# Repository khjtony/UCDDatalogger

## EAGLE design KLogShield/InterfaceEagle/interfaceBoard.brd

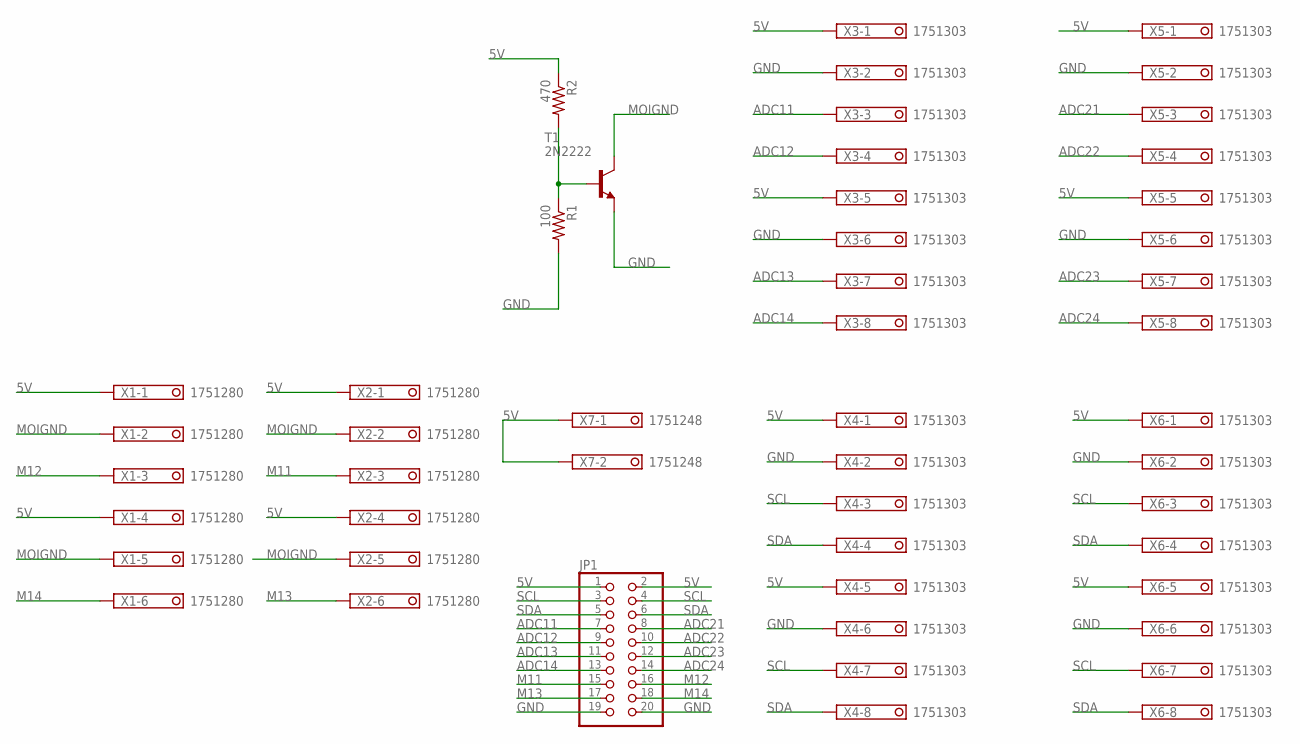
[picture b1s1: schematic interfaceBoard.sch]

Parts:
JP1: PINHD-2X10; 2X10
R1: 100; M0805
R2: 470; M0805
T1: 2N2222; TO92-EBC-OVAL
X1, X2: 1751280
X3, X4, X5, X6: 1751303
X7: 1751248

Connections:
5V: JP1.1, JP1.2, R2.1, X1.1, X1.4, X2.1, X2.4, X3.1, X3.5, X4.1, X4.5, X5.1, X5.5, X6.1, X6.5, X7.1, X7.2
ADC11: JP1.7, X3.3
ADC12: JP1.9, X3.4
ADC13: JP1.11, X3.7
ADC14: JP1.13, X3.8
ADC21: JP1.8, X5.3
ADC22: JP1.10, X5.4
ADC23: JP1.12, X5.7
ADC24: JP1.14, X5.8
GND: JP1.19, JP1.20, R1.2, T1.E, X3.2, X3.6, X4.2, X4.6, X5.2, X5.6, X6.2, X6.6
M11: JP1.15, X2.3
M12: JP1.16, X1.3
M13: JP1.17, X2.6
M14: JP1.18, X1.6
MOIGND: T1.C, X1.2, X1.5, X2.2, X2.5
unnamed: R1.1, R2.2, T1.B
SCL: JP1.3, JP1.4, X4.3, X4.7, X6.3, X6.7
SDA: JP1.5, JP1.6, X4.4, X4.8, X6.4, X6.8

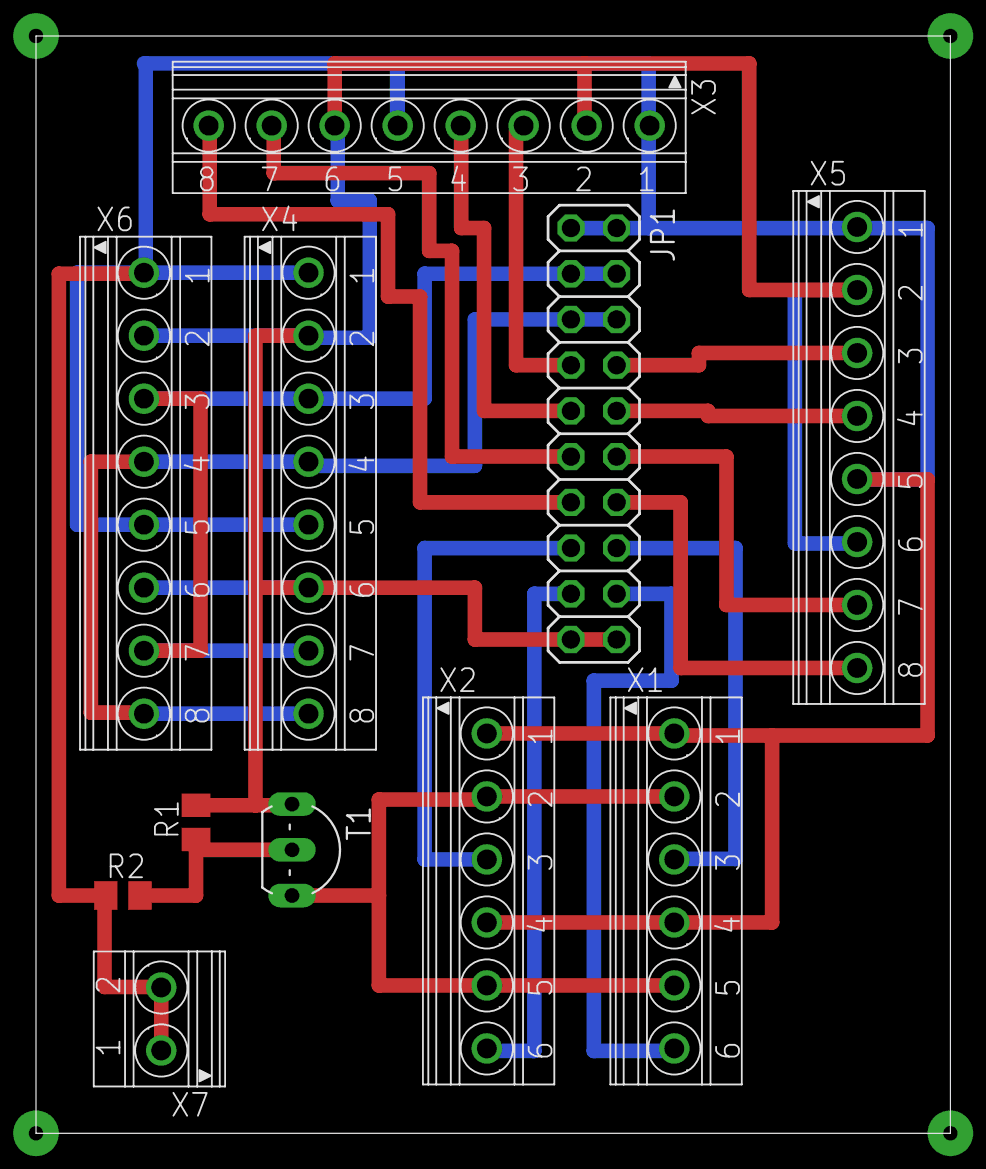
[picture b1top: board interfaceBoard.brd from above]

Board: 2 copper layers, 50.8 x 61.0 mm, 11 parts (0 on the bottom side), 18 nets.

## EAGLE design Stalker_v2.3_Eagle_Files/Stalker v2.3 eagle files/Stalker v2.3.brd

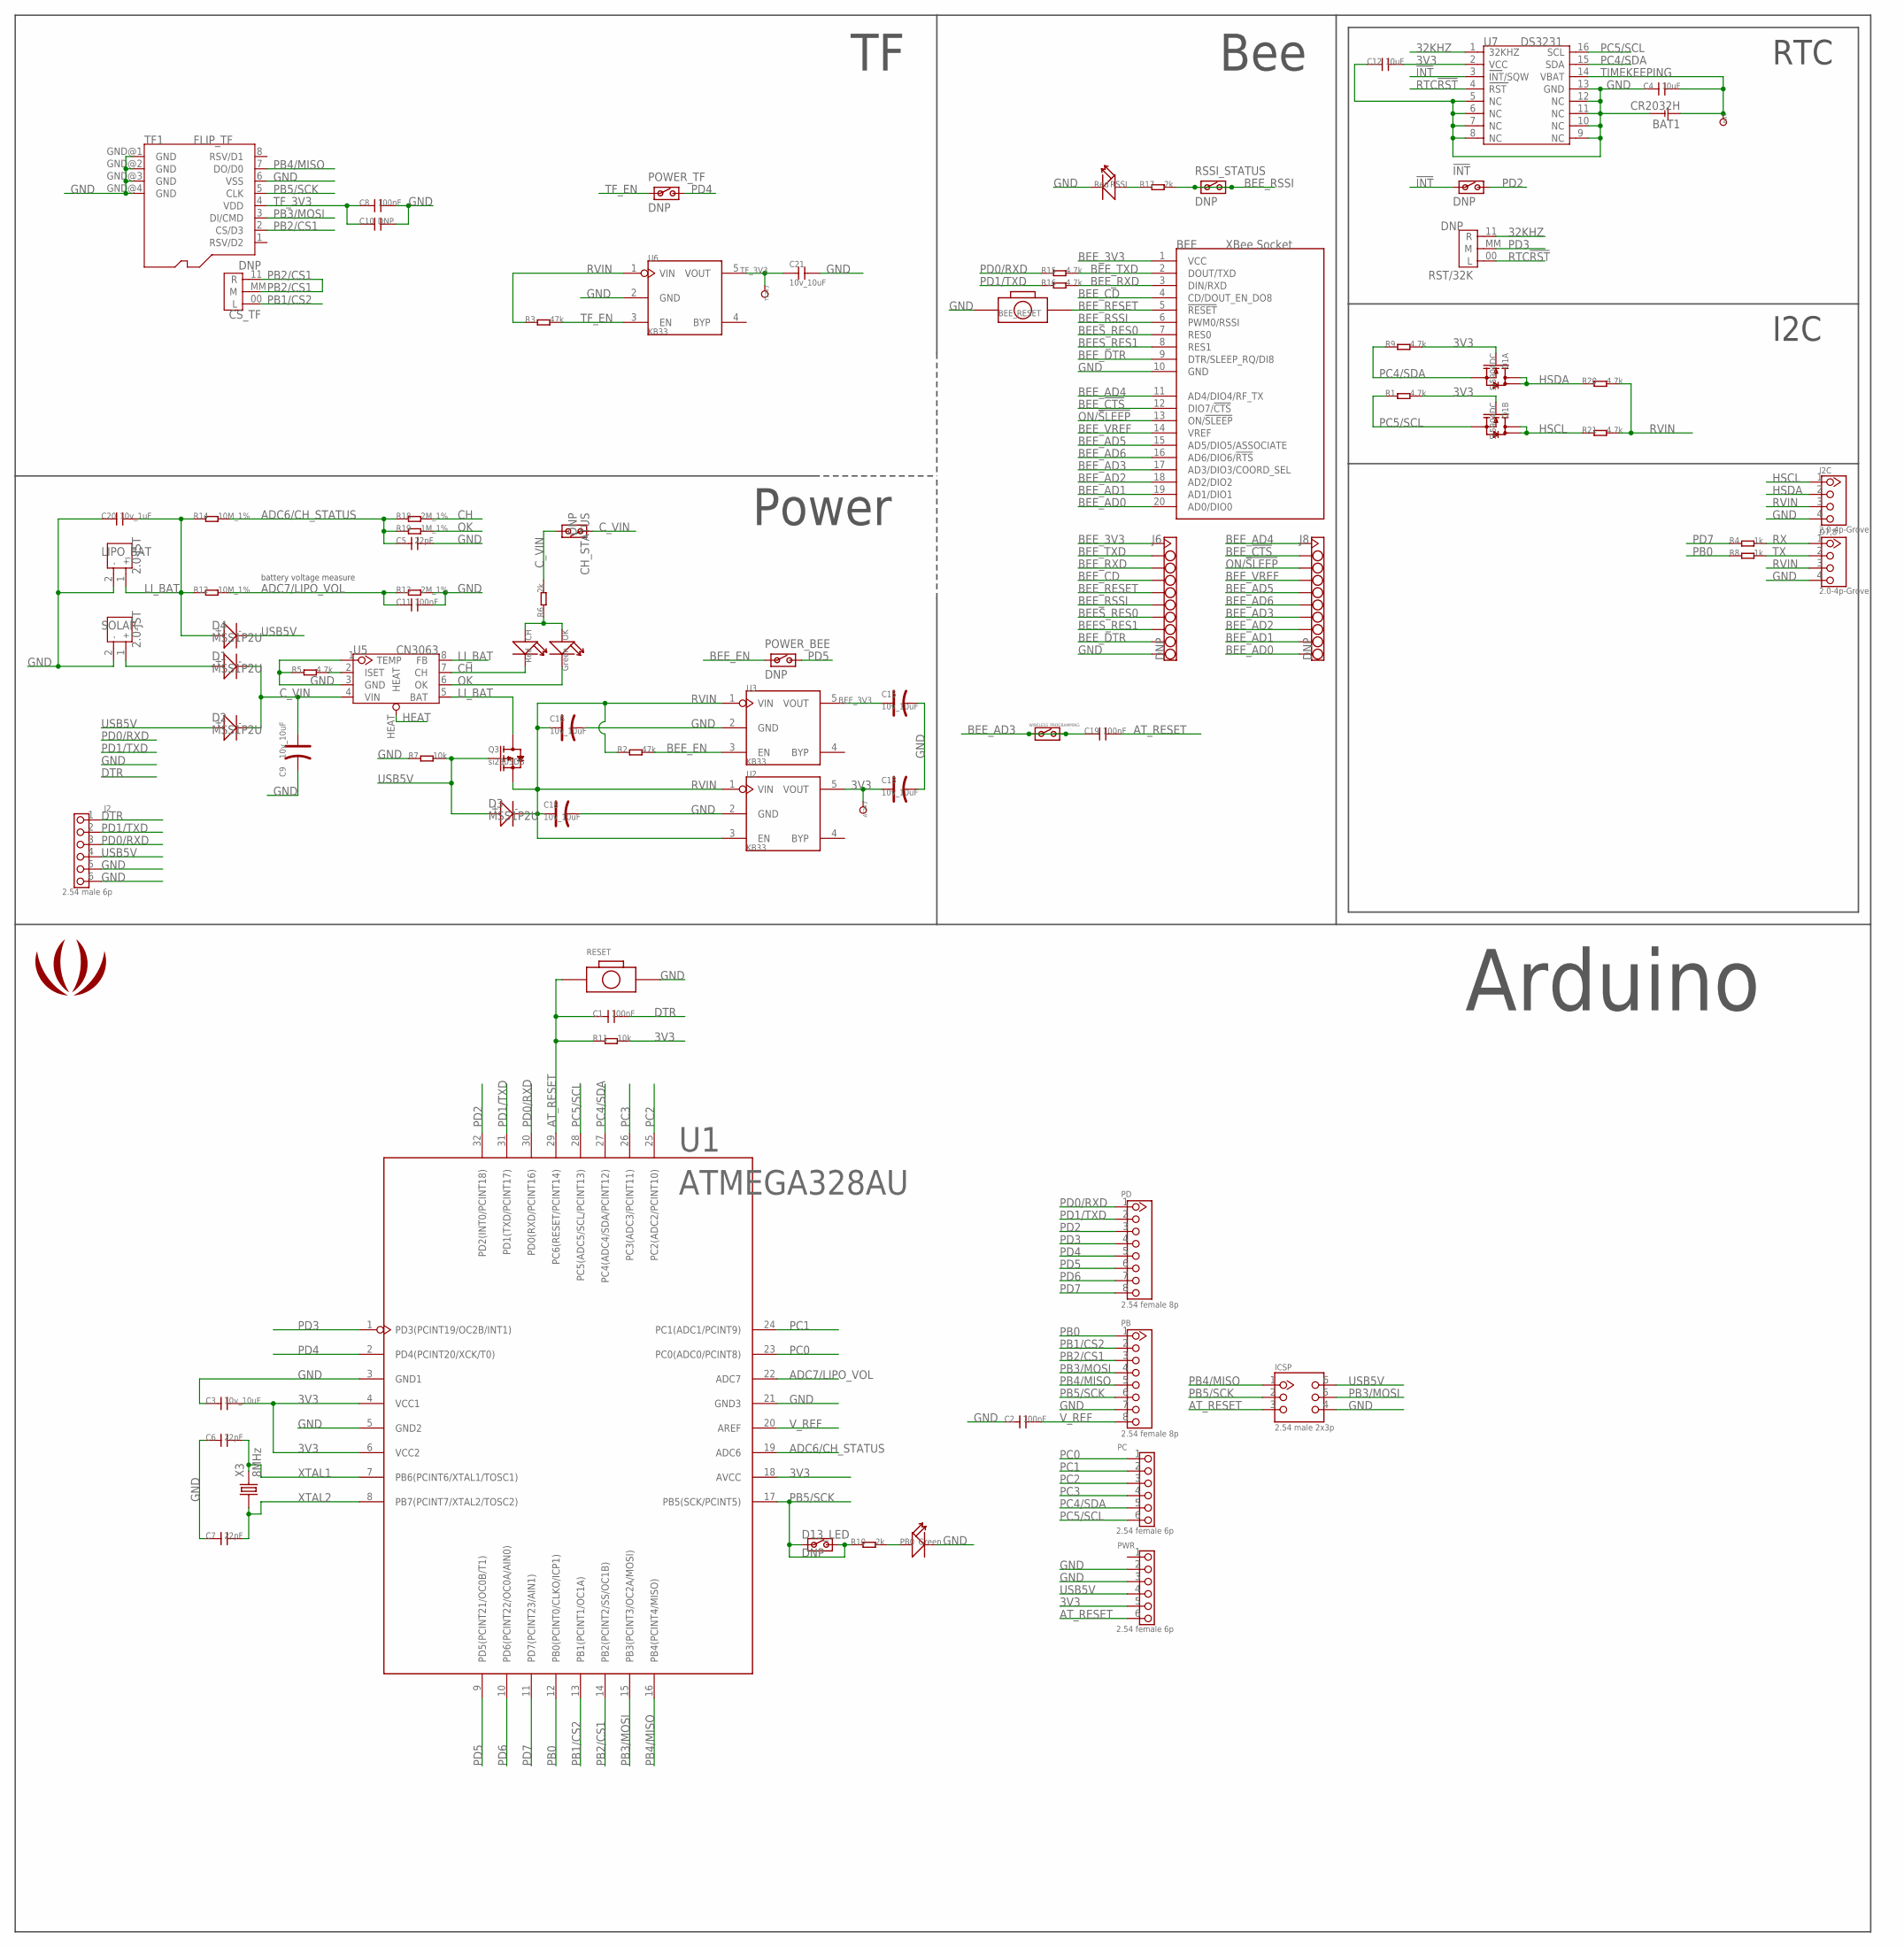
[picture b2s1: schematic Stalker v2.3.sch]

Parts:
!INT: DNP; JP_SW
AT3V3: DNP; TP_3535
BAT: DNP; TP_3535
BAT1: CR2032H
BEE: XBee Socket; BEE
BEE_RESET: 3.8x6.1 button; BOTTON_1
C1, C2, C8, C11, C19: 100nF; 0603
C3, C21: 10v_10uF; 0805
C4, C12: 10uF; 0805
C5, C6, C7: 22pF; 0603
C9, C13, C15, C16, C18: 10v_10uF; AVX-A
C10: DNP; 0603
C20: 10v_1uF; 0805
CH: Red; D0603
CH_STATUS: DNP; JP_SW
CS_TF: DNP; JUMPER
D1, D2, D3, D4: MSS1P2U; D1005
D7,8: 2.0-4p-Grove; 4P-2.0
D13_LED: DNP; JP_SW
I2C: 2.0-4p-Grove; 4P-2.0
ICSP: 2.54 male 2x3p; 2X3P-2.54-LEADED
J2: 2.54 male 6p; 6P-2.54-LEADED
J6, J8: DNP; HEADER_1X10
LIPO_BAT: 2.0-JST; JST-2.0
LOGO1: LOGO; LOGO_RO
OK: Green; D0603
PB: 2.54 female 8p; 8P-2.54-LEADED
PB0: Green; D0603
PC: 2.54 female 6p; 6P-2.54-LEADED
PD: 2.54 female 8p; 8P-2.54-LEADED
POWER_BEE: DNP; JP_SW
POWER_TF: DNP; JP_SW
PWR: 2.54 female 6p; 6P-2.54-LEADED
Q1: Si5904DC; 1206-8
Q3: si2305DS; SOT23
R1, R5, R9, R15, R16, R20, R21: 4.7k; 0603@1
R2, R3: 47k; 0603@1
R4, R8: 1k; 0603@1
R6, R10, R17: 2k; 0603@1
R7, R11: 10k; 0603@1
R12, R14: 10M_1%; 0603@1
R13, R18: 2M_1%; 0603@1
R19: 1M_1%; 0603@1
RESET: 3.8x6.1 button; BOTTON_1
RSSI: Red; D0603
RSSI_STATUS: DNP; JP_SW
RST/32K: DNP; JUMPER
SOLAR: 2.0-JST; JST-2.0
TF1: FLIP_TF
TF3V3: DNP; TP_3535
U1: ATMEGA328AU; ATMEGA168-20AU
U2, U3, U6: KB33; SOT23-5
U5: CN3063; SOP8
U7: DS3231; SO16-W
WIRELESS_PROGRAMMING: DNP; JP_SW
X3: 8MHz; HC49/S

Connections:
3V3: AT3V3.T, C3.2, C12.2, C13.+, PWR.5, Q1.2 (G), Q1.4 (G), R1.2, R9.2, R11.2, U1.4 (VCC1), U1.6 (VCC2), U1.18 (AVCC), U2.5 (VOUT), U7.2 (VCC)
32KHZ: RST/32K.11 (R), U7.1 (32KHZ)
!INT: !INT.1, U7.3 (INT/SQW)
ADC6/CH_STATUS: C5.1, R14.2, R18.1, R19.1, U1.19 (ADC6)
ADC7/LIPO_VOL: C11.1, R12.2, R13.1, U1.22 (ADC7)
AT_RESET: C1.1, C19.2, ICSP.3, PWR.6, R11.1, RESET.1, U1.29 (PC6(RESET/PCINT14))
BEES_RES0: BEE.7 (RES0), J6.7
BEES_RES1: BEE.8 (RES1), J6.8
BEE_3V3: BEE.1 (VCC), C15.+, J6.1, U3.5 (VOUT)
BEE_!CTS: BEE.12 (DIO7/!CTS), J8.2
BEE_AD0: BEE.20 (AD0/DIO0), J8.10
BEE_AD1: BEE.19 (AD1/DIO1), J8.9
BEE_AD2: BEE.18 (AD2/DIO2), J8.8
BEE_AD3: BEE.17 (AD3/DIO3/COORD_SEL), C19.1, J8.7, WIRELESS_PROGRAMMING.1, WIRELESS_PROGRAMMING.2
BEE_AD4: BEE.11 (AD4/DIO4/RF_TX), J8.1
BEE_AD5: BEE.15 (AD5/DIO5/ASSOCIATE), J8.5
BEE_AD6: BEE.16 (AD6/DIO6/!RTS), J8.6
BEE_CD: BEE.4 (CD/DOUT_EN_DO8), J6.4
BEE_DTR: BEE.9 (DTR/SLEEP_RQ/DI8), J6.9
BEE_EN: POWER_BEE.1, R2.2, U3.3 (EN)
BEE_RESET: BEE.5 (!RESET), BEE_RESET.P$2 (2), J6.5
BEE_RSSI: BEE.6 (PWM0/RSSI), J6.6, R17.2, RSSI_STATUS.1, RSSI_STATUS.2
BEE_RXD: BEE.3 (DIN/RXD), J6.3, R16.2
BEE_TXD: BEE.2 (DOUT/TXD), J6.2, R15.2
BEE_VREF: BEE.14 (VREF), J8.4
CH: CH.-, R18.2, U5.7 (CH)
C_VIN: C9.+, CH_STATUS.1, CH_STATUS.2, D1.-, D2.-, R6.2, U5.4 (VIN)
DTR: C1.2, J2.1
GND: BAT1.-, BEE.10 (GND), BEE_RESET.1, C2.1, C3.1, C4.1, C5.2, C6.1, C7.1, C8.2, C9.-, C10.2, C11.2, C12.1, C13.-, C15.-, C16.-, C18.-, C20.1, C21.2, D7,8.4, I2C.4, ICSP.4, J2.5, J2.6, J6.10, LIPO_BAT.2, PB.7, PB0.-, PWR.2, PWR.3, R5.1, R7.1, R13.2, RESET.P$2 (2), RSSI.-, SOLAR.2, TF1.6 (VSS), TF1.GND@1 (GND), TF1.GND@2 (GND), TF1.GND@3 (GND), TF1.GND@4 (GND), U1.3 (GND1), U1.5 (GND2), U1.21 (GND3), U2.2 (GND), U3.2 (GND), U5.1 (TEMP), U5.3 (GND), U6.2 (GND), U7.5 (NC), U7.6 (NC), U7.7 (NC), U7.8 (NC), U7.9 (NC), U7.10 (NC), U7.11 (NC), U7.12 (NC), U7.13 (GND)
HEAT: U5.HEAT
HSCL: I2C.1, Q1.5 (D), Q1.6 (D), R21.1
HSDA: I2C.2, Q1.7 (D), Q1.8 (D), R20.1
LI_BAT: C20.2, D4.+, LIPO_BAT.1, Q3.3 (D), R12.1, R14.1, U5.5 (BAT), U5.8 (FB)
unnamed: PB0.+, R10.2
unnamed: D1.+, SOLAR.1
unnamed: R5.2, U5.2 (ISET)
unnamed: R17.1, RSSI.+
unnamed: CH.+, OK.+, R6.1
OK: OK.-, R19.2, U5.6 (OK)
ON/!SLEEP: BEE.13 (ON/!SLEEP), J8.3
PB0: PB.1, R8.1, U1.12 (PB0(PCINT0/CLKO/ICP1))
PB1/CS2: CS_TF.00 (L), PB.2, U1.13 (PB1(PCINT1/OC1A))
PB2/CS1: CS_TF.11 (R), CS_TF.MM (M), PB.3, TF1.2 (CS/D3), U1.14 (PB2(PCINT2/SS/OC1B))
PB3/MOSI: ICSP.5, PB.4, TF1.3 (DI/CMD), U1.15 (PB3(PCINT3/OC2A/MOSI))
PB4/MISO: ICSP.1, PB.5, TF1.7 (DO/D0), U1.16 (PB4(PCINT4/MISO))
PB5/SCK: D13_LED.1, D13_LED.2, ICSP.2, PB.6, R10.1, TF1.5 (CLK), U1.17 (PB5(SCK/PCINT5))
PC0: PC.1, U1.23 (PC0(ADC0/PCINT8))
PC1: PC.2, U1.24 (PC1(ADC1/PCINT9))
PC2: PC.3, U1.25 (PC2(ADC2/PCINT10))
PC3: PC.4, U1.26 (PC3(ADC3/PCINT11))
PC4/SDA: PC.5, Q1.1 (S), R9.1, U1.27 (PC4(ADC4/SDA/PCINT12)), U7.15 (SDA)
PC5/SCL: PC.6, Q1.3 (S), R1.1, U1.28 (PC5(ADC5/SCL/PCINT13)), U7.16 (SCL)
PD0/RXD: J2.3, PD.1, R15.1, U1.30 (PD0(RXD/PCINT16))
PD1/TXD: J2.2, PD.2, R16.1, U1.31 (PD1(TXD/PCINT17))
PD2: !INT.2, PD.3, U1.32 (PD2(INT0/PCINT18))
PD3: PD.4, RST/32K.MM (M), U1.1 (PD3(PCINT19/OC2B/INT1))
PD4: PD.5, POWER_TF.2, U1.2 (PD4(PCINT20/XCK/T0))
PD5: PD.6, POWER_BEE.2, U1.9 (PD5(PCINT21/OC0B/T1))
PD6: PD.7, U1.10 (PD6(PCINT22/OC0A/AIN0))
PD7: PD.8, R4.1, U1.11 (PD7(PCINT23/AIN1))
RTC!RST: RST/32K.00 (L), U7.4 (RST)
RVIN: C16.+, C18.+, D3.-, D7,8.3, I2C.3, Q3.2 (S), R2.1, R3.1, R20.2, R21.2, U2.1 (VIN), U2.3 (EN), U3.1 (VIN), U6.1 (VIN)
RX: D7,8.1, R4.2
TF_3V3: C8.1, C10.1, C21.1, TF1.4 (VDD), TF3V3.T, U6.5 (VOUT)
TF_EN: POWER_TF.1, R3.2, U6.3 (EN)
TIMEKEEPING: BAT.T, BAT1.+, C4.2, U7.14 (VBAT)
TX: D7,8.2, R8.2
USB5V: D2.+, D3.+, D4.-, ICSP.6, J2.4, PWR.4, Q3.1 (G), R7.2
V_REF: C2.2, PB.8, U1.20 (AREF)
XTAL1: C6.2, U1.7 (PB6(PCINT6/XTAL1/TOSC1)), X3.2
XTAL2: C7.2, U1.8 (PB7(PCINT7/XTAL2/TOSC2)), X3.1

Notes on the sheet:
Power
Arduino
Bee
battery voltage measure
RTC
I2C

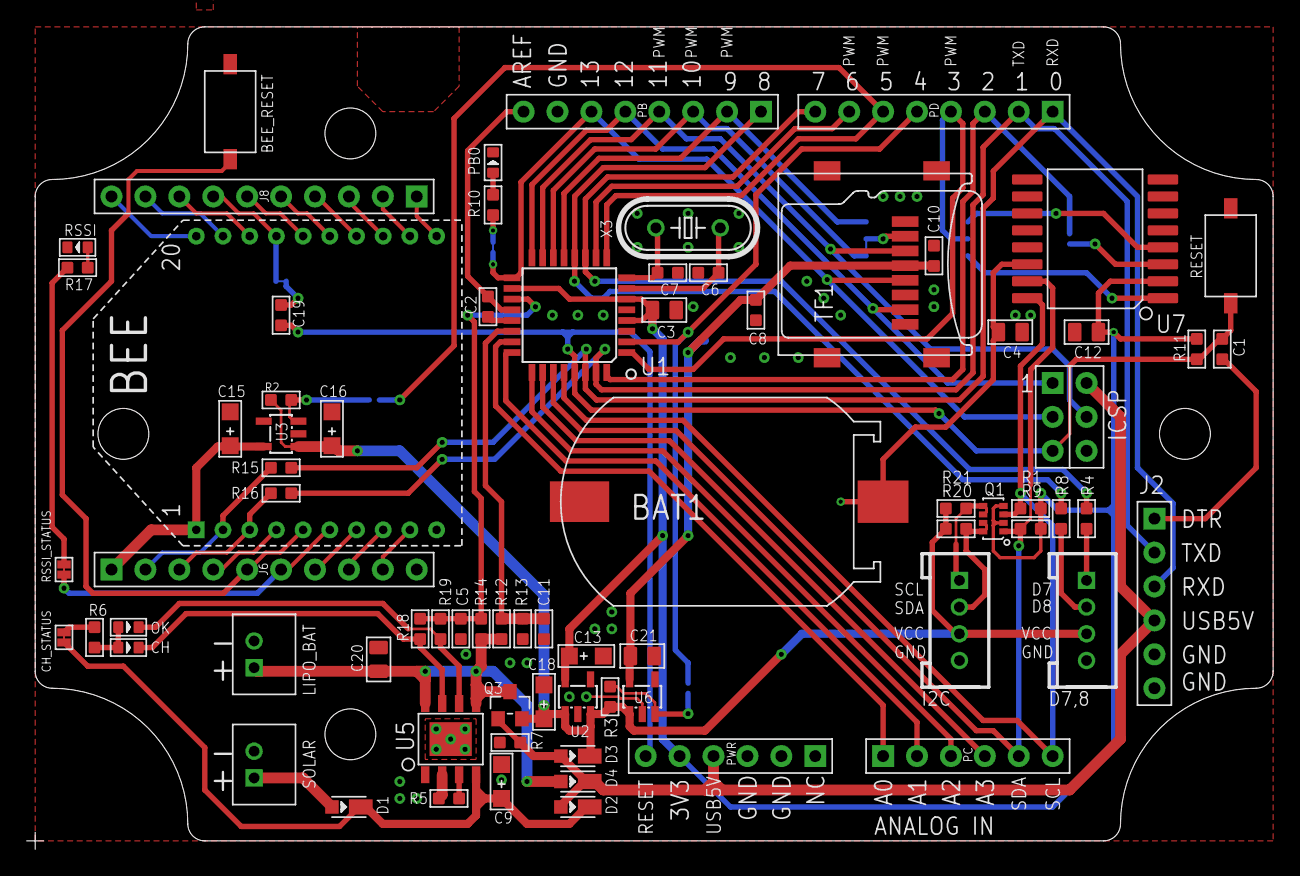
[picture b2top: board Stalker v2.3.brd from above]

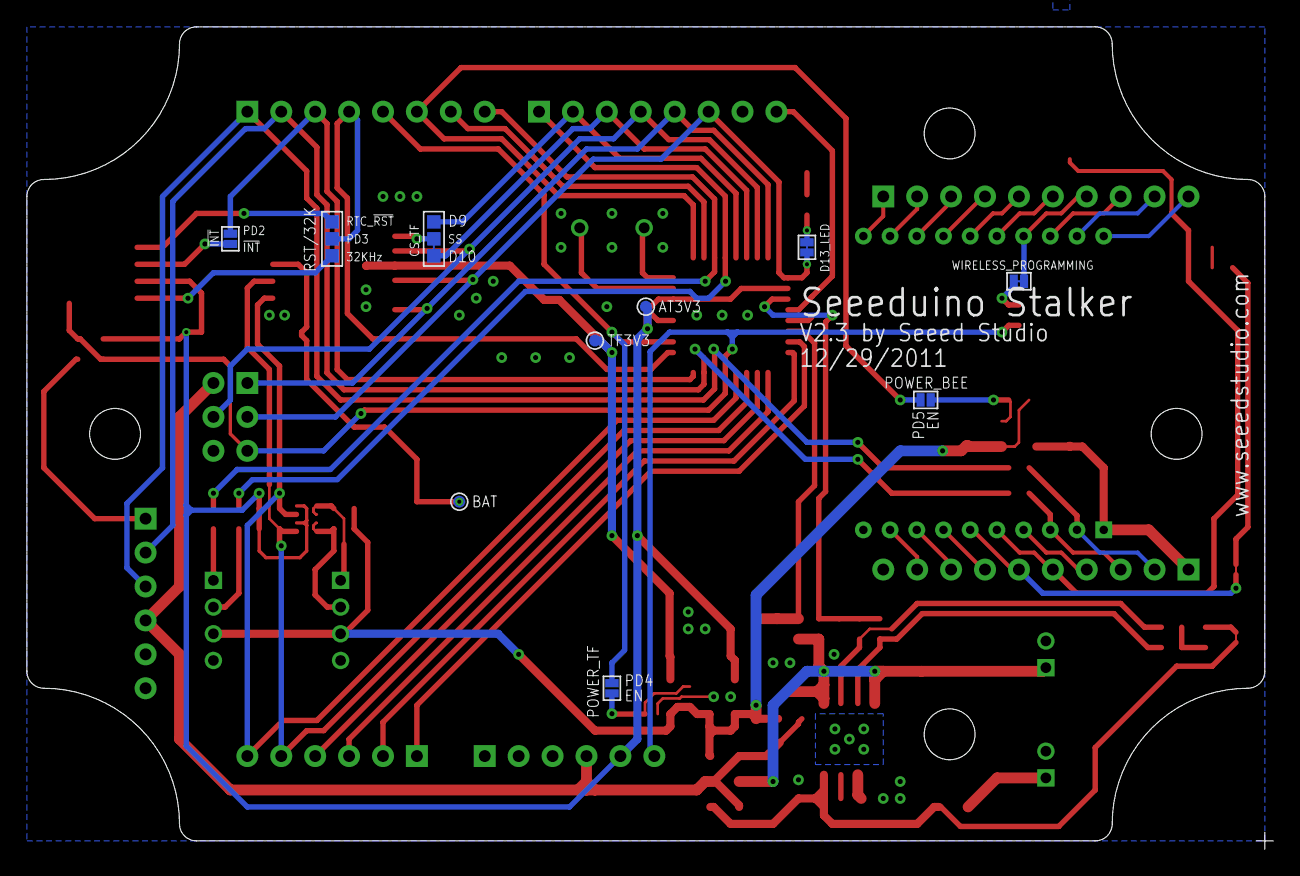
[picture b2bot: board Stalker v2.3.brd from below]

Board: 2 copper layers, 93.3 x 61.6 mm, 87 parts (10 on the bottom side), 70 nets.

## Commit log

2015-02-02 initialize new repo for current project
2015-02-02 working on kLogCollection lib
2015-02-05 move work on anotehr
2015-02-05 finish RX test files
2015-02-05 finish master ver 001
2015-02-22 added frame sample
2015-02-22 added gitignore
2015-02-22 start klog
2015-03-27 new k shield
2015-03-30 new generation of logger software
2015-03-30 upload_log
2015-07-05 final product start
2015-07-05 klogshield revison 2
2015-07-06 need to finish coordinator
2015-07-15 no xbee
2015-07-19 documents
2015-07-20 version 1.0 report
2015-07-20 minor change on firmware
2015-07-20 version 1.0 doc finished
2015-07-22 klog interface board gen2
2015-07-22 program finished
